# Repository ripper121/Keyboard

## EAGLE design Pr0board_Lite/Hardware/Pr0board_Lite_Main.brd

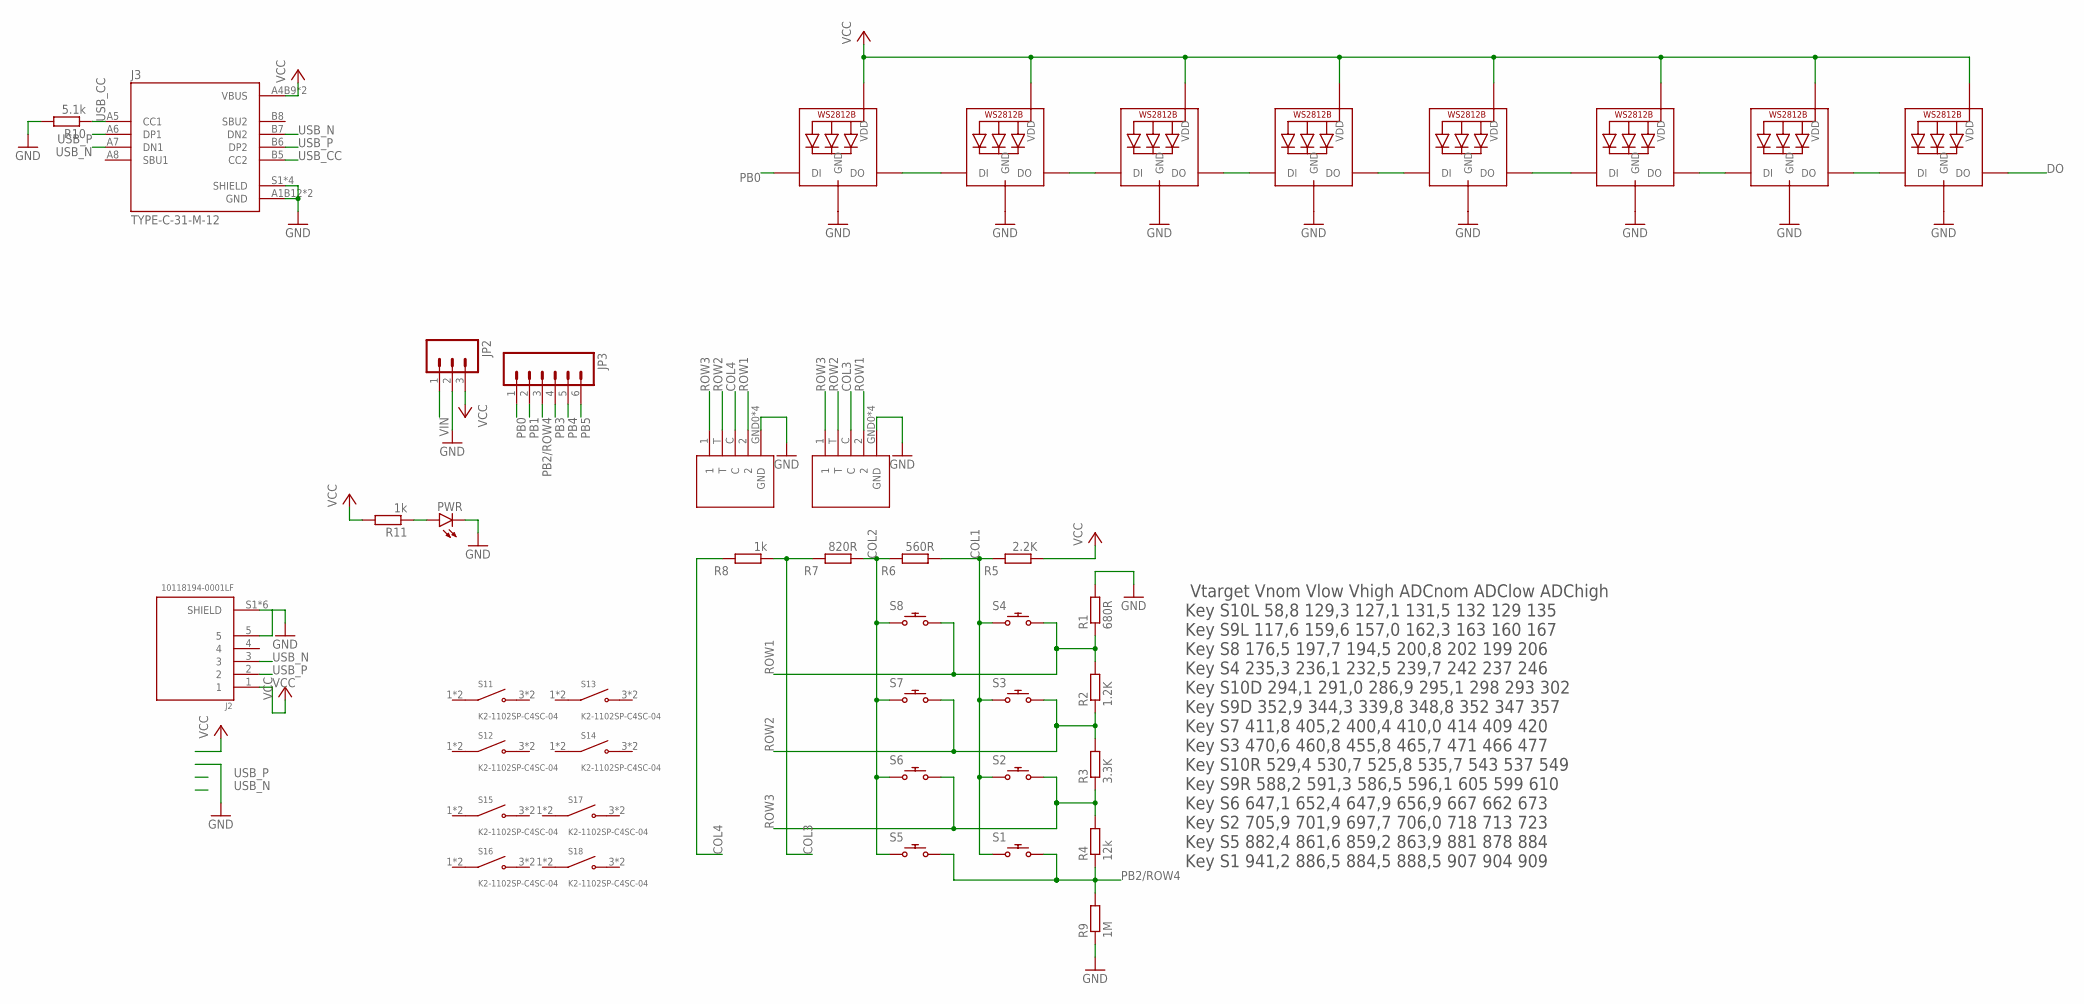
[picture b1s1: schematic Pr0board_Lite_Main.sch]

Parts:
J2: 10118194-0001LF; AMPHENOL_10118194-0001LF
J3: TYPE-C-31-M-12; HRO_TYPE-C-31-M-12
JP2: M03PTH; 1X03
JP3: M06SIP; 1X06
LED1, LED2, LED3, LED4, LED5, LED6, LED7, LED8: WS2812B3535; LED3535
PWR: LEDCHIP-LED0805; CHIP-LED0805
R1: 680R; R0805
R2: 1.2K; R0805
R3: 3.3K; R0805
R4: 12k; R0805
R5: 2.2K; R0805
R6: 560R; R0805
R7: 820R; R0805
R8, R11: 1k; R0805
R9: 1M; R0805
R10: 5.1k; R0805
S1, S2, S3, S4, S5, S6, S7, S8: CPG151101S13 C404353; CHERRY_MX_LED
S9, S10: TM-2024A
S11, S12, S13, S14, S15, S16, S17, S18: K2-1102SP-C4SC-04; SW_2-1437565-9

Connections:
COL1: R5.2, R6.1, S1.S1 (1), S2.S1 (1), S3.S1 (1), S4.S1 (1)
COL2: R6.2, R7.1, S5.S1 (1), S6.S1 (1), S7.S1 (1), S8.S1 (1)
COL3: R7.2, R8.1, S9.C
COL4: R8.2, S10.C
DO: LED7.2 (DO)
GND: J2.5, J2.S1 (SHIELD), J2.S2 (SHIELD), J2.S3 (SHIELD), J2.S4 (SHIELD), J2.S5 (SHIELD), J2.S6 (SHIELD), J3.A1B12 (GND), J3.B1A12 (GND), J3.S1 (SHIELD), J3.S2 (SHIELD), J3.S3 (SHIELD), J3.S4 (SHIELD), JP2.2, LED1.3 (GND), LED2.3 (GND), LED3.3 (GND), LED4.3 (GND), LED5.3 (GND), LED6.3 (GND), LED7.3 (GND), LED8.3 (GND), PWR.C, R1.2, R9.1, R10.2, S9.GND0 (GND), S9.GND1 (GND), S9.GND2 (GND), S9.GND3 (GND), S10.GND0 (GND), S10.GND1 (GND), S10.GND2 (GND), S10.GND3 (GND)
unnamed: LED1.2 (DO), LED3.4 (DI)
unnamed: LED4.2 (DO), LED5.4 (DI)
unnamed: LED1.4 (DI), LED2.2 (DO)
unnamed: LED3.2 (DO), LED4.4 (DI)
unnamed: PWR.A, R11.1
unnamed: LED5.2 (DO), LED6.4 (DI)
unnamed: LED6.2 (DO), LED8.4 (DI)
unnamed: LED7.4 (DI), LED8.2 (DO)
PB0: JP3.1, LED2.4 (DI)
PB1: JP3.2
PB2/ROW4: JP3.3, R4.1, R9.2, S1.S2 (2), S5.S2 (2)
PB3: JP3.4
PB4: JP3.5
PB5: JP3.6
ROW1: R1.1, R2.2, S4.S2 (2), S8.S2 (2), S9.2, S10.2
ROW2: R2.1, R3.2, S3.S2 (2), S7.S2 (2), S9.T, S10.T
ROW3: R3.1, R4.2, S2.S2 (2), S6.S2 (2), S9.1, S10.1
USB_CC: J3.A5 (CC1), J3.B5 (CC2), R10.1
USB_N: J2.3, J3.A7 (DN1), J3.B7 (DN2)
USB_P: J2.2, J3.A6 (DP1), J3.B6 (DP2)
VCC: J2.1, J3.A4B9 (VBUS), J3.B4A9 (VBUS), JP2.3, LED1.1 (VDD), LED2.1 (VDD), LED3.1 (VDD), LED4.1 (VDD), LED5.1 (VDD), LED6.1 (VDD), LED7.1 (VDD), LED8.1 (VDD), R5.1, R11.2
VIN: JP2.1

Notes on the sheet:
Vtarget Vnom Vlow Vhigh ADCnom ADClow ADChigh Key S10L 58,8 129,3 127,1 131,5 132 129 135 Key S9L 117,6 159,6 157,0 162,3 163 160 167 Key S8 176,5 197,7 194,5 200,8 202 199 206 Key S4 235,3 236,1 232,5 239,7 242 237 246 Key S10D 294,1 291,0 286,9 295,1 298 293 302 Key S9D 352,9 344,3 339,8 348,8 35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

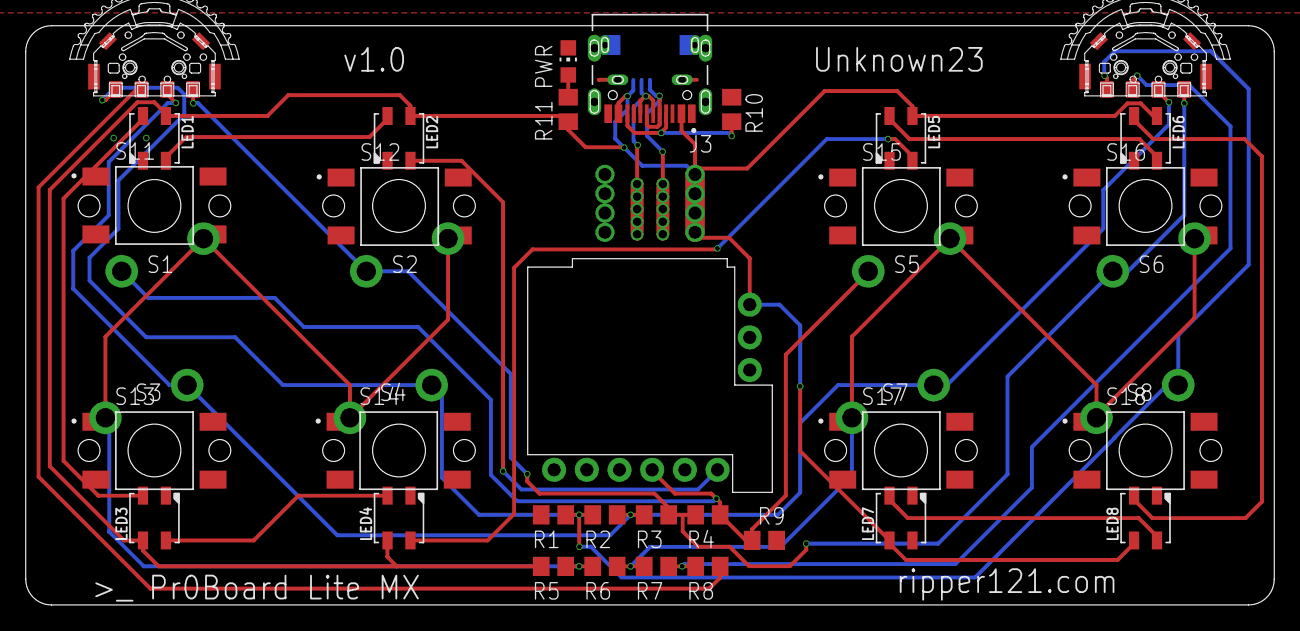
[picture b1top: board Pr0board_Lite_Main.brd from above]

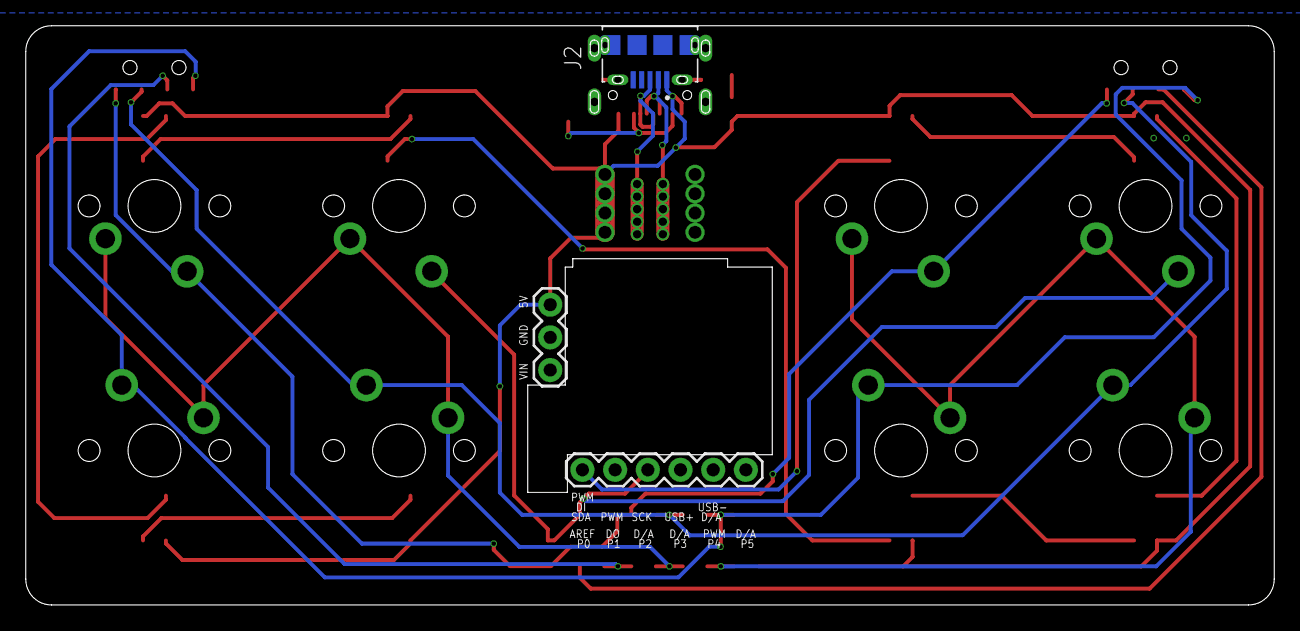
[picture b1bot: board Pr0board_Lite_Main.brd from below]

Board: 2 copper layers, 97.0 x 45.0 mm, 42 parts (3 on the bottom side), 22 nets.

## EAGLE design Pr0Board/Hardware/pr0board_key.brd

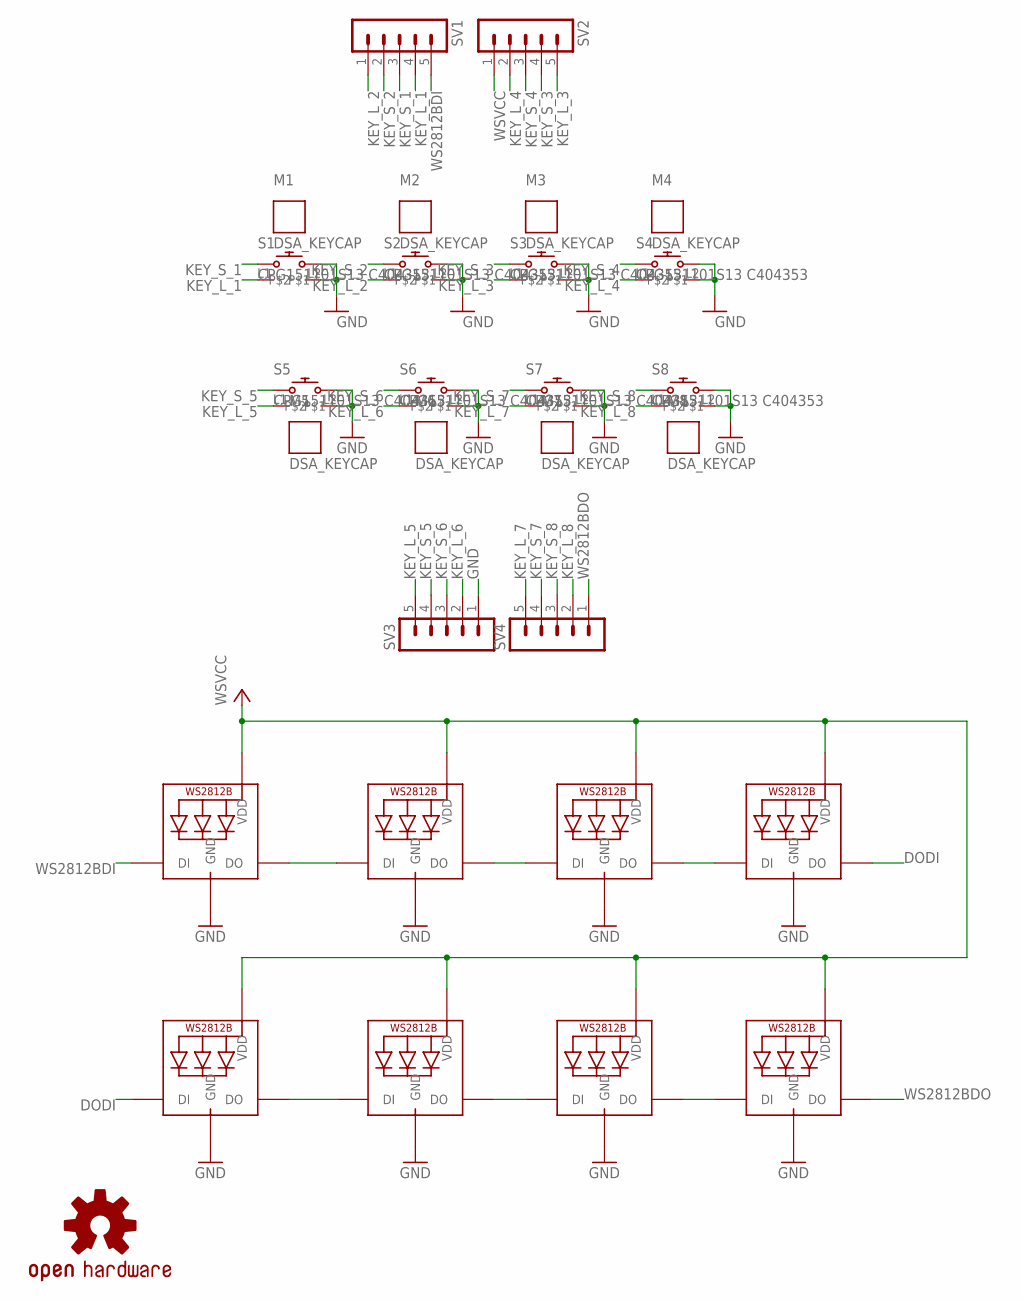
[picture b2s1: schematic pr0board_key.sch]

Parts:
LED1, LED2, LED3, LED4, LED5, LED6, LED7, LED8: WS2812B3535; LED3535
M1, M2, M3, M4, M5, M6, M7, M8: DSA_KEYCAP
S1, S2, S3, S4, S5, S6, S7, S8: CPG151101S13 C404353; CHERRY_MX_LED
SV1, SV2, SV3, SV4: MA05-1
U$1: OSHW-LOGOS; OSHW-LOGO-S

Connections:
DODI: LED4.2 (DO), LED5.4 (DI)
GND: LED1.3 (GND), LED2.3 (GND), LED3.3 (GND), LED4.3 (GND), LED5.3 (GND), LED6.3 (GND), LED7.3 (GND), LED8.3 (GND), S1.L2, S1.S2 (2), S2.L2, S2.S2 (2), S3.L2, S3.S2 (2), S4.L2, S4.S2 (2), S5.L2, S5.S2 (2), S6.L2, S6.S2 (2), S7.L2, S7.S2 (2), S8.L2, S8.S2 (2), SV3.1
KEY_L_1: S1.L1, SV1.4
KEY_L_2: S2.L1, SV1.1
KEY_L_3: S3.L1, SV2.5
KEY_L_4: S4.L1, SV2.2
KEY_L_5: S5.L1, SV3.5
KEY_L_6: S6.L1, SV3.2
KEY_L_7: S7.L1, SV4.5
KEY_L_8: S8.L1, SV4.2
KEY_S_1: S1.S1 (1), SV1.3
KEY_S_2: S2.S1 (1), SV1.2
KEY_S_3: S3.S1 (1), SV2.4
KEY_S_4: S4.S1 (1), SV2.3
KEY_S_5: S5.S1 (1), SV3.4
KEY_S_6: S6.S1 (1), SV3.3
KEY_S_7: S7.S1 (1), SV4.4
KEY_S_8: S8.S1 (1), SV4.3
unnamed: LED1.2 (DO), LED2.4 (DI)
unnamed: LED2.2 (DO), LED3.4 (DI)
unnamed: LED3.2 (DO), LED4.4 (DI)
unnamed: LED5.2 (DO), LED6.4 (DI)
unnamed: LED6.2 (DO), LED7.4 (DI)
unnamed: LED7.2 (DO), LED8.4 (DI)
WS2812BDI: LED1.4 (DI), SV1.5
WS2812BDO: LED8.2 (DO), SV4.1
WSVCC: LED1.1 (VDD), LED2.1 (VDD), LED3.1 (VDD), LED4.1 (VDD), LED5.1 (VDD), LED6.1 (VDD), LED7.1 (VDD), LED8.1 (VDD), SV2.1

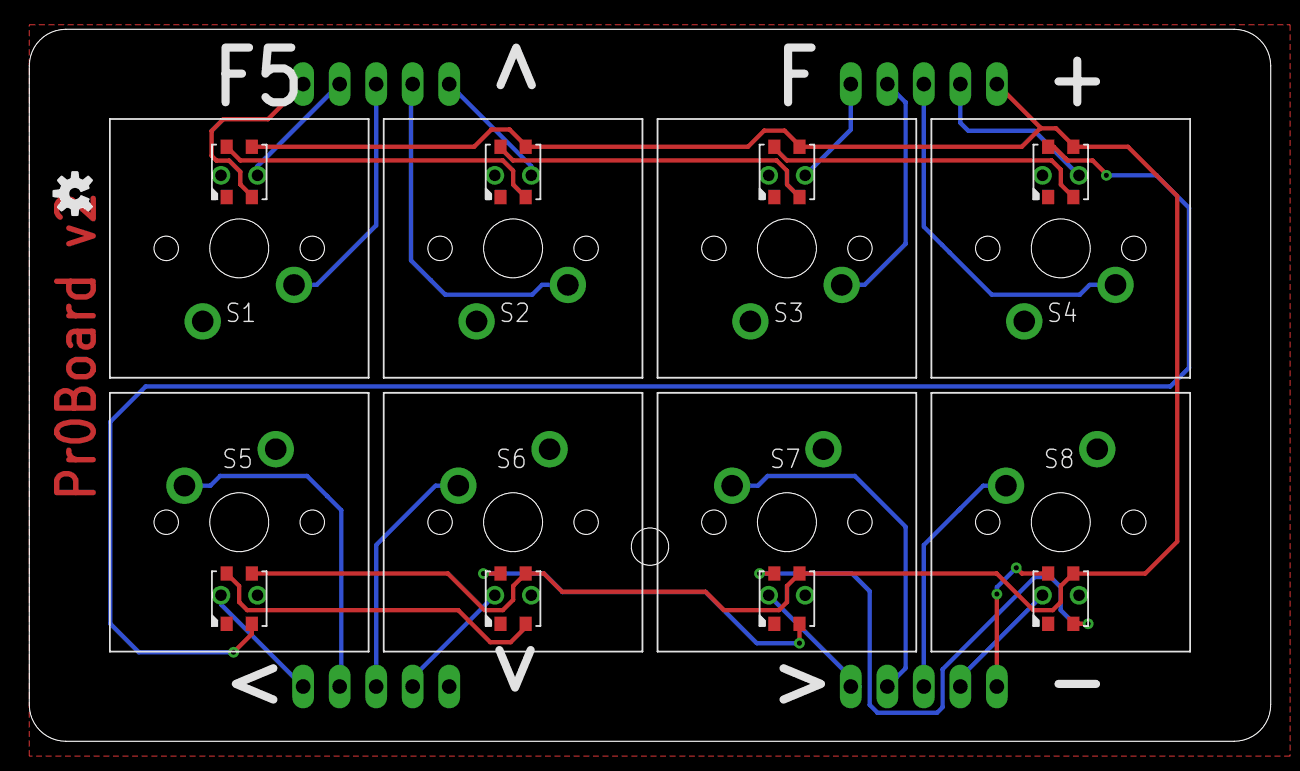
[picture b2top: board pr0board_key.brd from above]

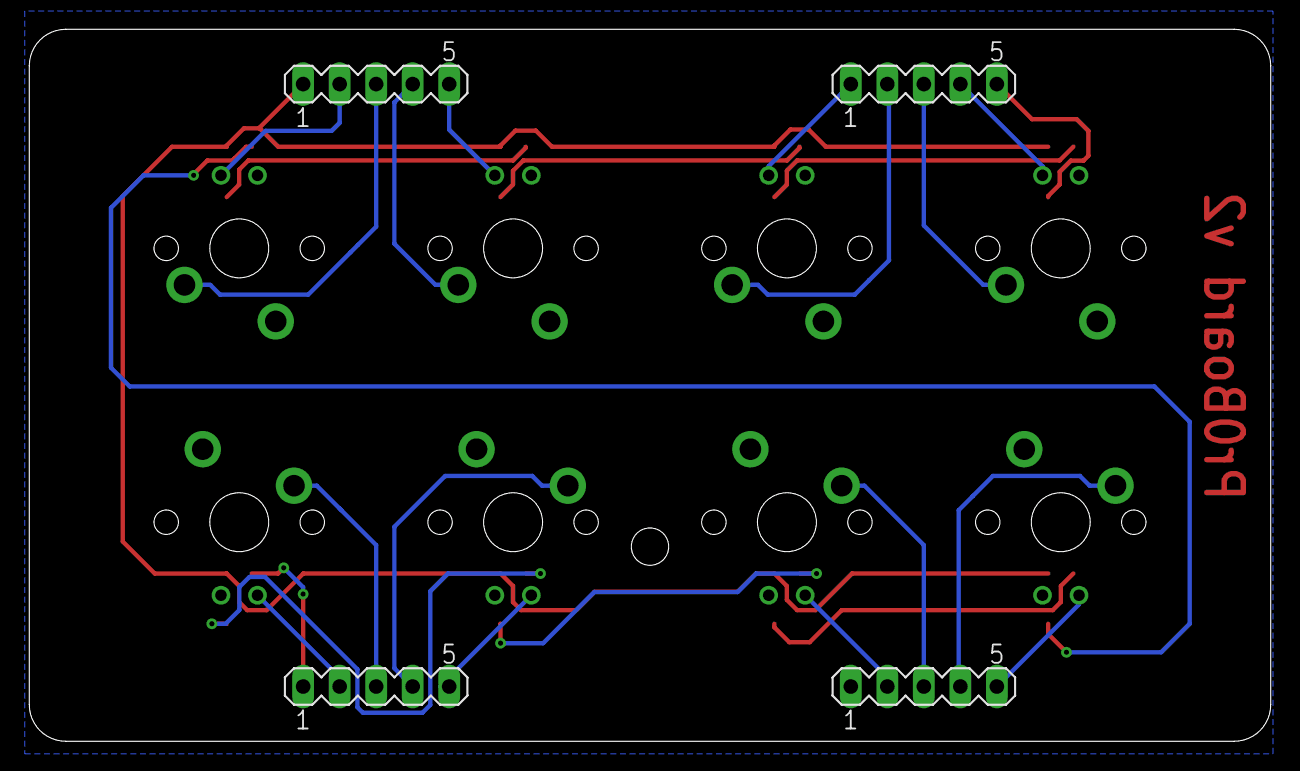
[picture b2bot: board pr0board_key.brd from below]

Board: 2 copper layers, 86.4 x 49.5 mm, 29 parts (4 on the bottom side), 27 nets.

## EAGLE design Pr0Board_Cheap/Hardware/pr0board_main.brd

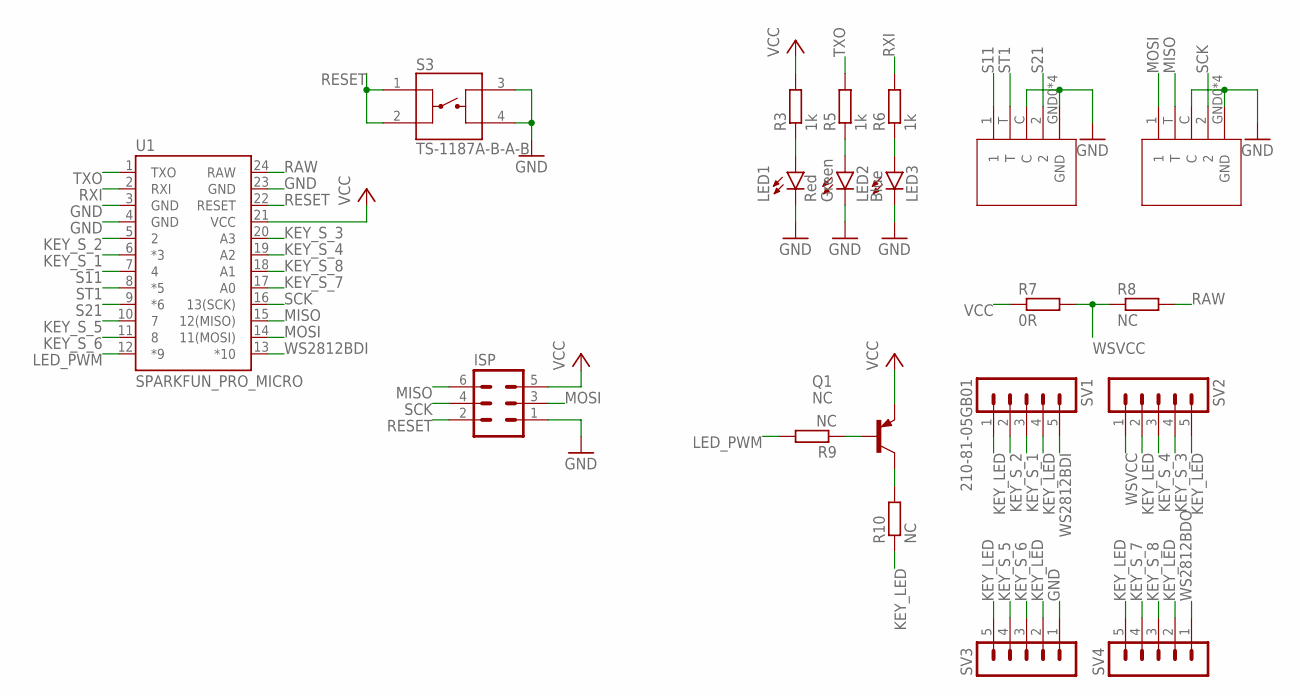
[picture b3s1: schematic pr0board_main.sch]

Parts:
ISP: MA03-2
LED1: Red; CHIP-LED0603
LED2: Green; CHIP-LED0603
LED3: Blue; CHIP-LED0603
Q1: NC; SOT23
R3, R5, R6: 1k; R0603
R7: 0R; R0603
R8, R9: NC; R0603
R10: NC; R0805
S1, S2: TM-2024A
S3: TS-1187A-B-A-B; SW_PTS525SM15SMTR2LFS
SV1: 210-81-05GB01; MA05-1
SV2, SV3, SV4: MA05-1
U1: SPARKFUN_PRO_MICRO

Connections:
GND: ISP.1, LED1.C, LED2.C, LED3.C, S1.C, S1.GND0 (GND), S1.GND1 (GND), S1.GND2 (GND), S1.GND3 (GND), S2.C, S2.GND0 (GND), S2.GND1 (GND), S2.GND2 (GND), S2.GND3 (GND), S3.3, S3.4, SV3.1, U1.3 (GND), U1.4 (GND), U1.23 (GND)
KEY_LED: R10.1, SV1.1, SV1.4, SV2.2, SV2.5, SV3.2, SV3.5, SV4.2, SV4.5
KEY_S_1: SV1.3, U1.6 (*3)
KEY_S_2: SV1.2, U1.5 (2)
KEY_S_3: SV2.4, U1.20 (A3)
KEY_S_4: SV2.3, U1.19 (A2)
KEY_S_5: SV3.4, U1.10 (7)
KEY_S_6: SV3.3, U1.11 (8)
KEY_S_7: SV4.4, U1.17 (A0)
KEY_S_8: SV4.3, U1.18 (A1)
LED_PWM: R9.2, U1.12 (*9)
MISO: ISP.6, S2.T, U1.15 (12(MISO))
MOSI: ISP.3, S2.1, U1.14 (11(MOSI))
unnamed: LED2.A, R5.1
unnamed: LED3.A, R6.1
unnamed: LED1.A, R3.1
unnamed: Q1.1 (B), R9.1
unnamed: Q1.3 (C), R10.2
RAW: R8.2, U1.24 (RAW)
RESET: ISP.2, S3.1, S3.2, U1.22 (RESET)
RXI: R6.2, U1.2 (RXI)
S11: S1.1, U1.7 (4)
S21: S1.2, U1.9 (*6)
SCK: ISP.4, S2.2, U1.16 (13(SCK))
ST1: S1.T, U1.8 (*5)
TXO: R5.2, U1.1 (TXO)
VCC: ISP.5, Q1.2 (E), R3.2, R7.1, U1.21 (VCC)
WS2812BDI: SV1.5, U1.13 (*10)
WS2812BDO: SV4.1
WSVCC: R7.2, R8.1, SV2.1

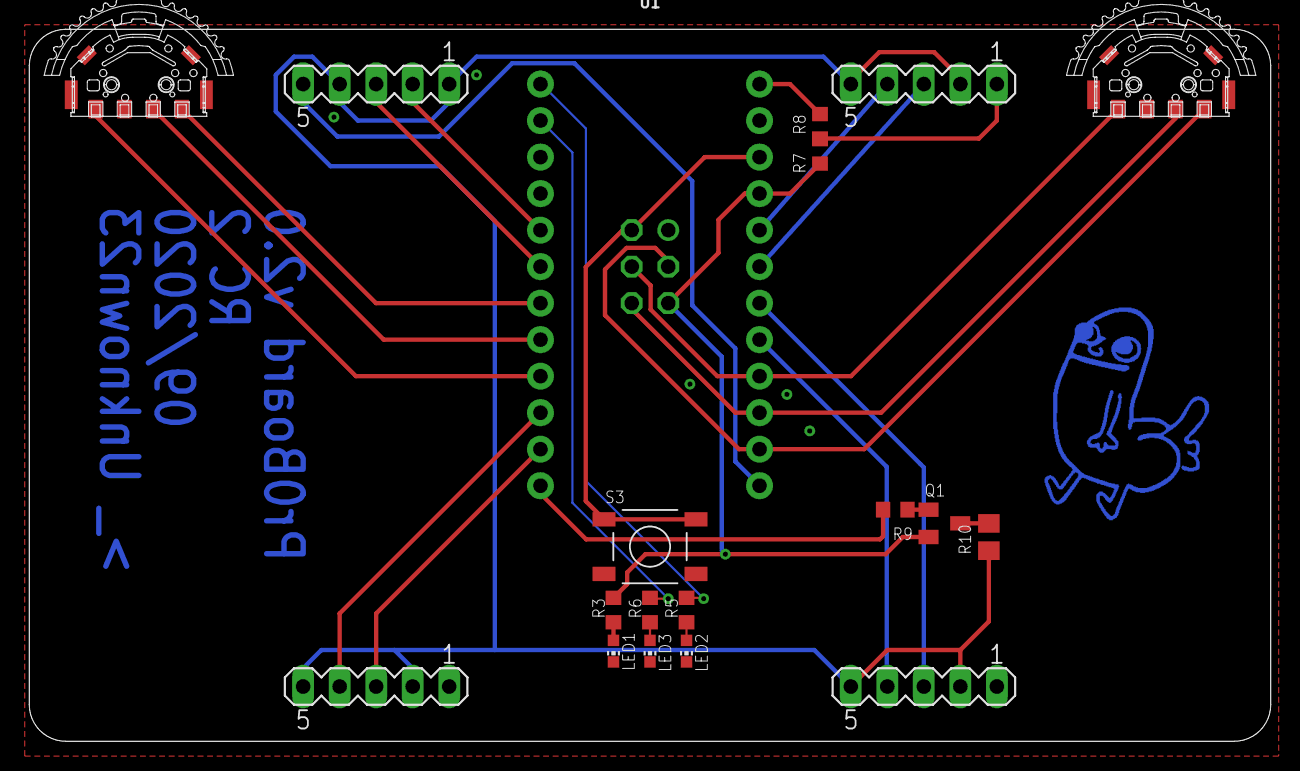
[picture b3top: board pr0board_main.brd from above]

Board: 2 copper layers, 86.4 x 49.5 mm, 20 parts (1 on the bottom side), 29 nets.

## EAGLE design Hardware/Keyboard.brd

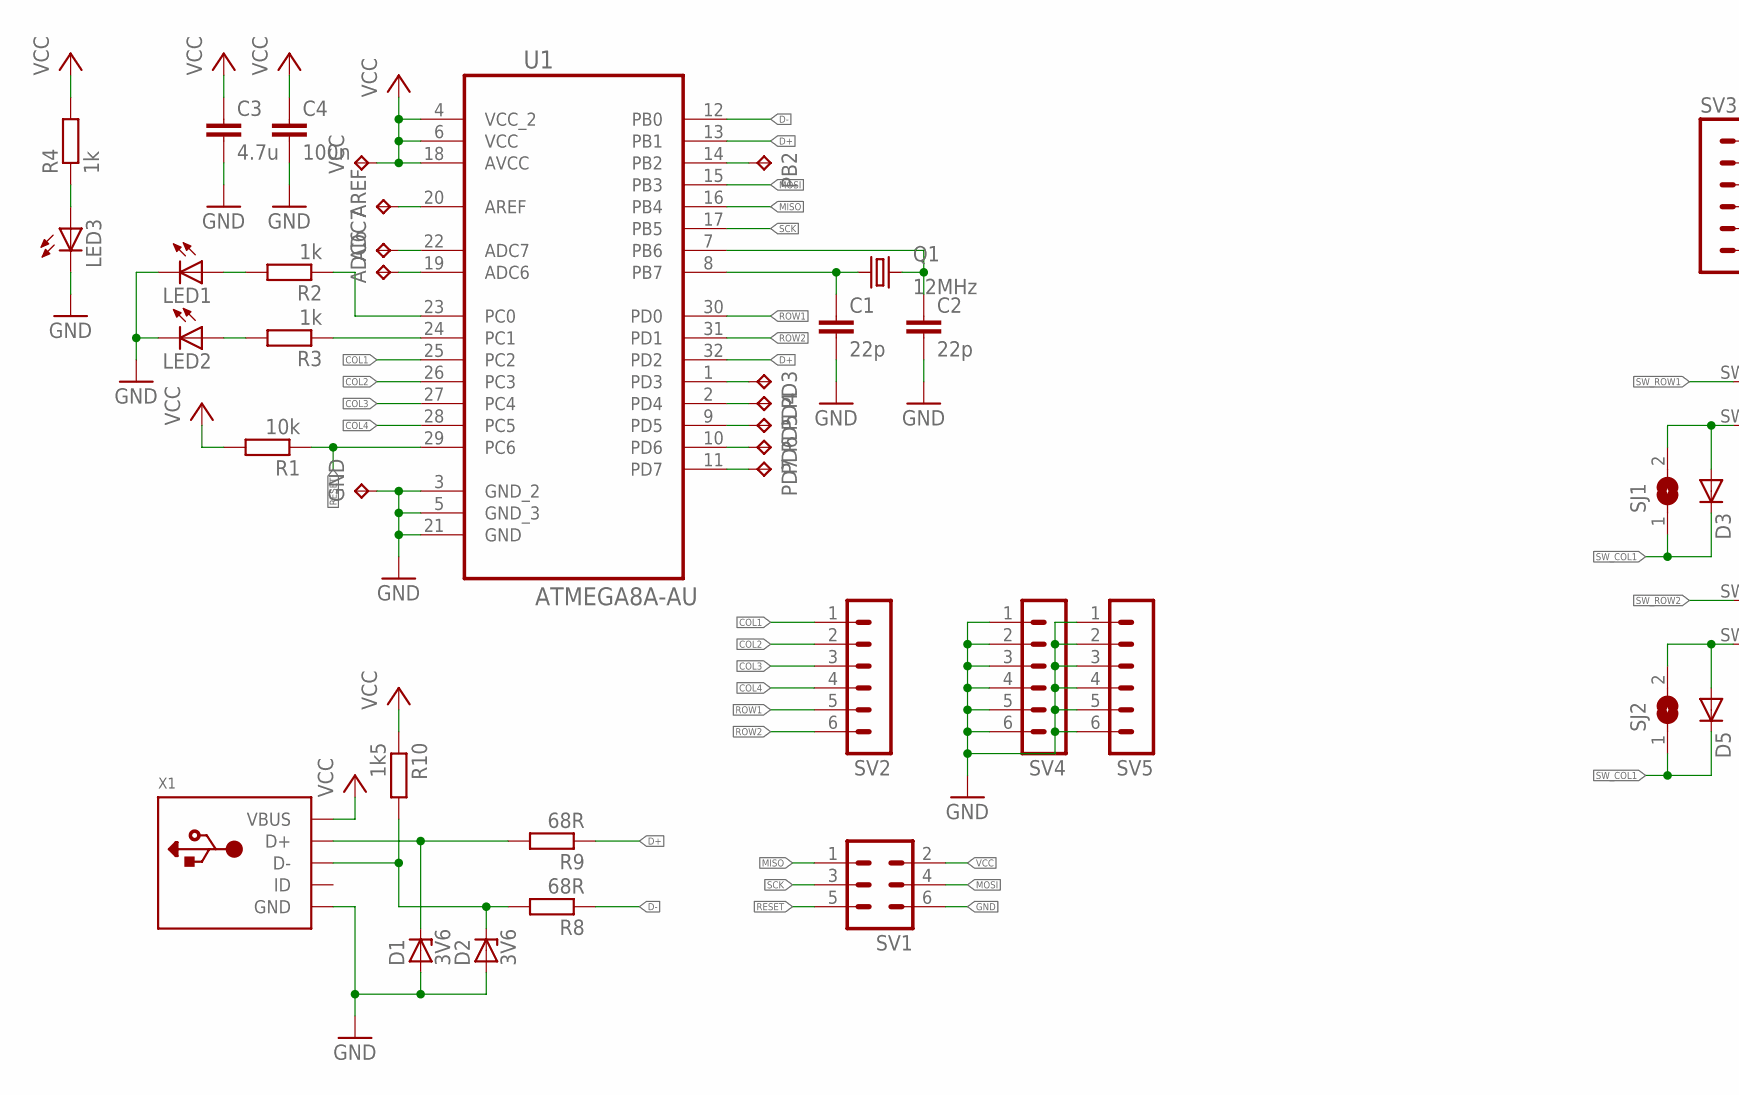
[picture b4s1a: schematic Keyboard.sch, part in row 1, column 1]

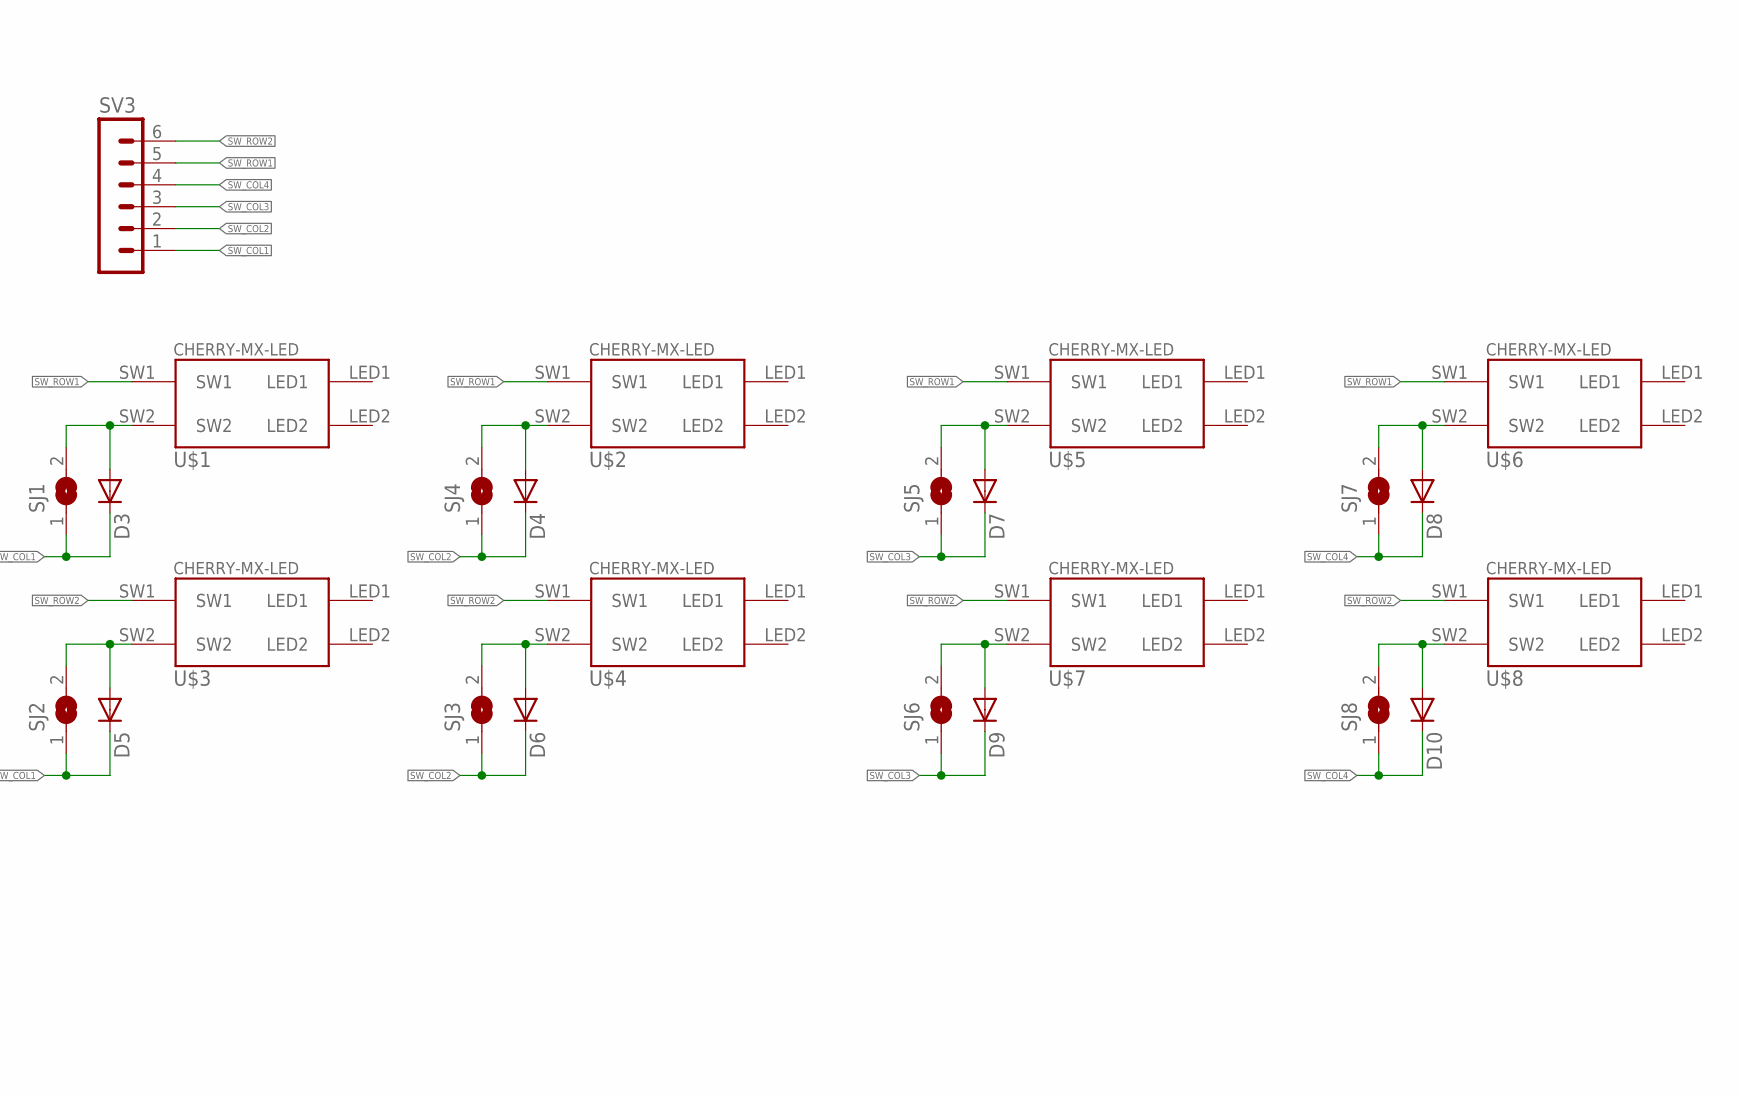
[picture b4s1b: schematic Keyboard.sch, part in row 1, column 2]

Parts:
ADC6, ADC7: TPB1,27; B1,27
AREF: TPB1,27; B1,27
C1, C2: 22p; C0603
C3: 4.7u; C0603
C4: 100n; C0603
D1, D2: 3V6; SOD80C
D3, D4, D5, D6, D7, D8, D9, D10: DIODE-MINIMELF; MINIMELF
GND: TPB1,27; B1,27
LED1, LED2, LED3: LEDCHIP-LED0603; CHIP-LED0603
PB2: TPB1,27; B1,27
PD3, PD4, PD5, PD6, PD7: TPB1,27; B1,27
Q1: 12MHz; 11.4X4.5
R1: 10k; R0603
R2, R3, R4: 1k; R0603
R8, R9: 68R; R0603
R10: 1k5; R0603
SJ1, SJ2, SJ3, SJ4, SJ5, SJ6, SJ7, SJ8: SJCLOSED; SJC
SV1: MA03-2
SV2, SV3, SV4, SV5: MA06-1
U1: ATMEGA8A-AU; QFP80P900X900X120-32N
U$1, U$2, U$3, U$4, U$5, U$6, U$7, U$8: CHERRY-MX-LED
VCC: TPB1,27; B1,27
X1: USB_MICRO_20329_V2; 4UCONN_20329_V2

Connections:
COL1: SV2.1, U1.25 (PC2)
COL2: SV2.2, U1.26 (PC3)
COL3: SV2.3, U1.27 (PC4)
COL4: SV2.4, U1.28 (PC5)
D+: R9.1, U1.13 (PB1), U1.32 (PD2)
D-: R8.1, U1.12 (PB0)
GND: C1.2, C2.2, C3.2, C4.2, D1.A, D2.A, GND.TP, LED1.C, LED2.C, LED3.C, SV1.6, SV4.1, SV4.2, SV4.3, SV4.4, SV4.5, SV4.6, SV5.1, SV5.2, SV5.3, SV5.4, SV5.5, SV5.6, U1.3 (GND_2), U1.5 (GND_3), U1.21 (GND), X1.BASE@1 (GND), X1.BASE@2 (GND), X1.GND, X1.SPRT@1 (GND), X1.SPRT@2 (GND), X1.SPRT@3 (GND), X1.SPRT@4 (GND)
MISO: SV1.1, U1.16 (PB4)
MOSI: SV1.4, U1.15 (PB3)
unnamed: C1.1, Q1.1, U1.8 (PB7)
unnamed: C2.1, Q1.2, U1.7 (PB6)
unnamed: LED3.A, R4.1
unnamed: R3.1, U1.24 (PC1)
unnamed: R2.1, U1.23 (PC0)
unnamed: LED1.A, R2.2
unnamed: LED2.A, R3.2
unnamed: D1.C, R9.2, X1.D+
unnamed: D2.C, R8.2, R10.2, X1.D-
unnamed: PD7.TP, U1.11 (PD7)
unnamed: D3.A, SJ1.2, U$1.SW2
unnamed: D5.A, SJ2.2, U$3.SW2
unnamed: PD6.TP, U1.10 (PD6)
unnamed: D4.A, SJ4.2, U$2.SW2
unnamed: PD5.TP, U1.9 (PD5)
unnamed: D6.A, SJ3.2, U$4.SW2
unnamed: PD4.TP, U1.2 (PD4)
unnamed: D7.A, SJ5.2, U$5.SW2
unnamed: PD3.TP, U1.1 (PD3)
unnamed: D9.A, SJ6.2, U$7.SW2
unnamed: AREF.TP, U1.20 (AREF)
unnamed: D8.A, SJ7.2, U$6.SW2
unnamed: ADC7.TP, U1.22 (ADC7)
unnamed: D10.A, SJ8.2, U$8.SW2
unnamed: ADC6.TP, U1.19 (ADC6)
unnamed: PB2.TP, U1.14 (PB2)
RESET: R1.1, SV1.5, U1.29 (PC6)
ROW1: SV2.5, U1.30 (PD0)
ROW2: SV2.6, U1.31 (PD1)
SCK: SV1.3, U1.17 (PB5)
SW_COL1: D3.C, D5.C, SJ1.1, SJ2.1, SV3.1
SW_COL2: D4.C, D6.C, SJ3.1, SJ4.1, SV3.2
SW_COL3: D7.C, D9.C, SJ5.1, SJ6.1, SV3.3
SW_COL4: D8.C, D10.C, SJ7.1, SJ8.1, SV3.4
SW_ROW1: SV3.5, U$1.SW1, U$2.SW1, U$5.SW1, U$6.SW1
SW_ROW2: SV3.6, U$3.SW1, U$4.SW1, U$7.SW1, U$8.SW1
VCC: C3.1, C4.1, R1.2, R4.2, R10.1, SV1.2, U1.4 (VCC_2), U1.6 (VCC), U1.18 (AVCC), VCC.TP, X1.VBUS

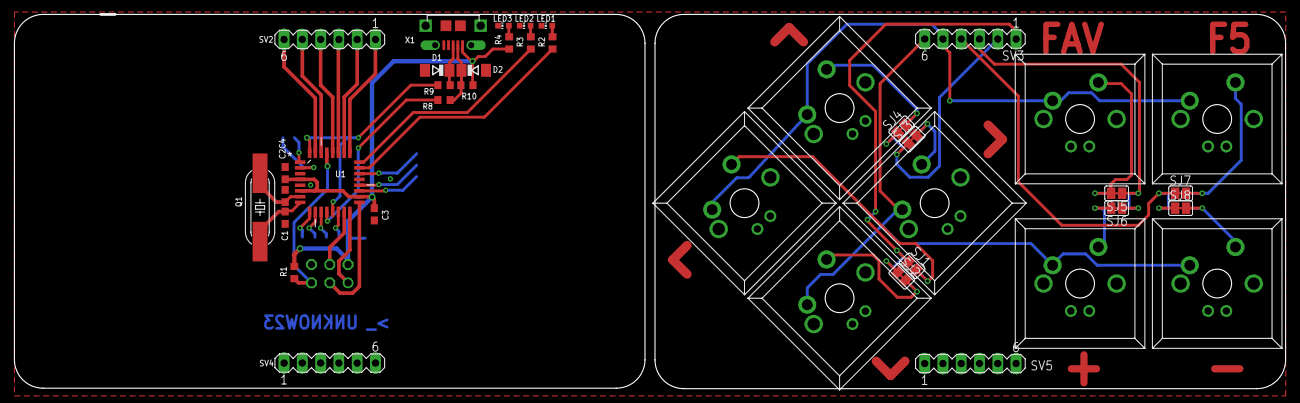
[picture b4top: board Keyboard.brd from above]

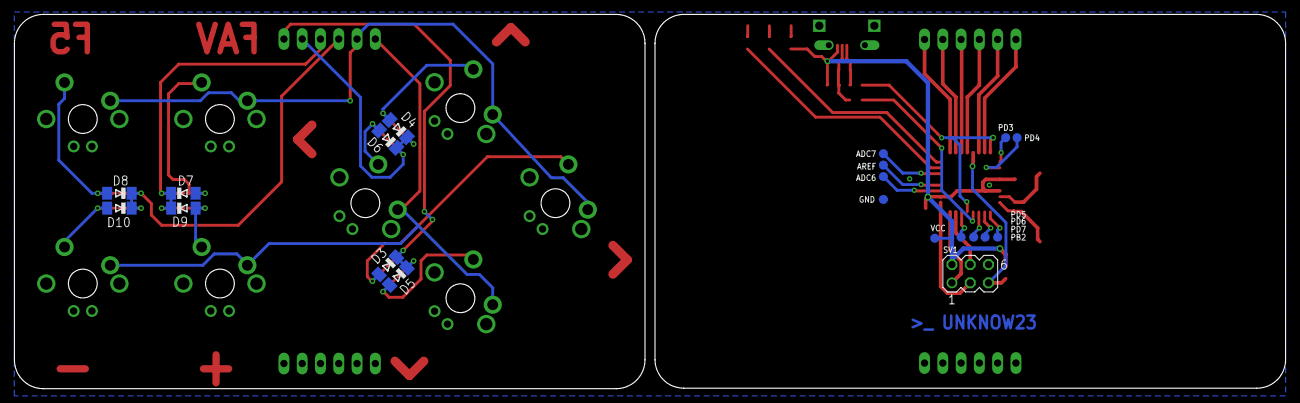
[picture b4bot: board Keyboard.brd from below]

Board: 2 copper layers, 176.6 x 52.0 mm, 59 parts (20 on the bottom side), 46 nets.

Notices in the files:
Firmware/KeyboadC/main.c:
Copyright: (c) 2014 by Ripper121
License: GNU GPL v2 (see License.txt)
parts and their libraries:
crystal-geyer_V1_0: Copyright: Geyer-Electronic
SparkFun-Boards: Licensing: Creative Commons ShareAlike 4.0 International - https://creativecommons.org/licenses/by-sa/4.0
SparkFun: Licensing: CC v3.0 Share-Alike You are welcome to use this library for commercial purposes.
